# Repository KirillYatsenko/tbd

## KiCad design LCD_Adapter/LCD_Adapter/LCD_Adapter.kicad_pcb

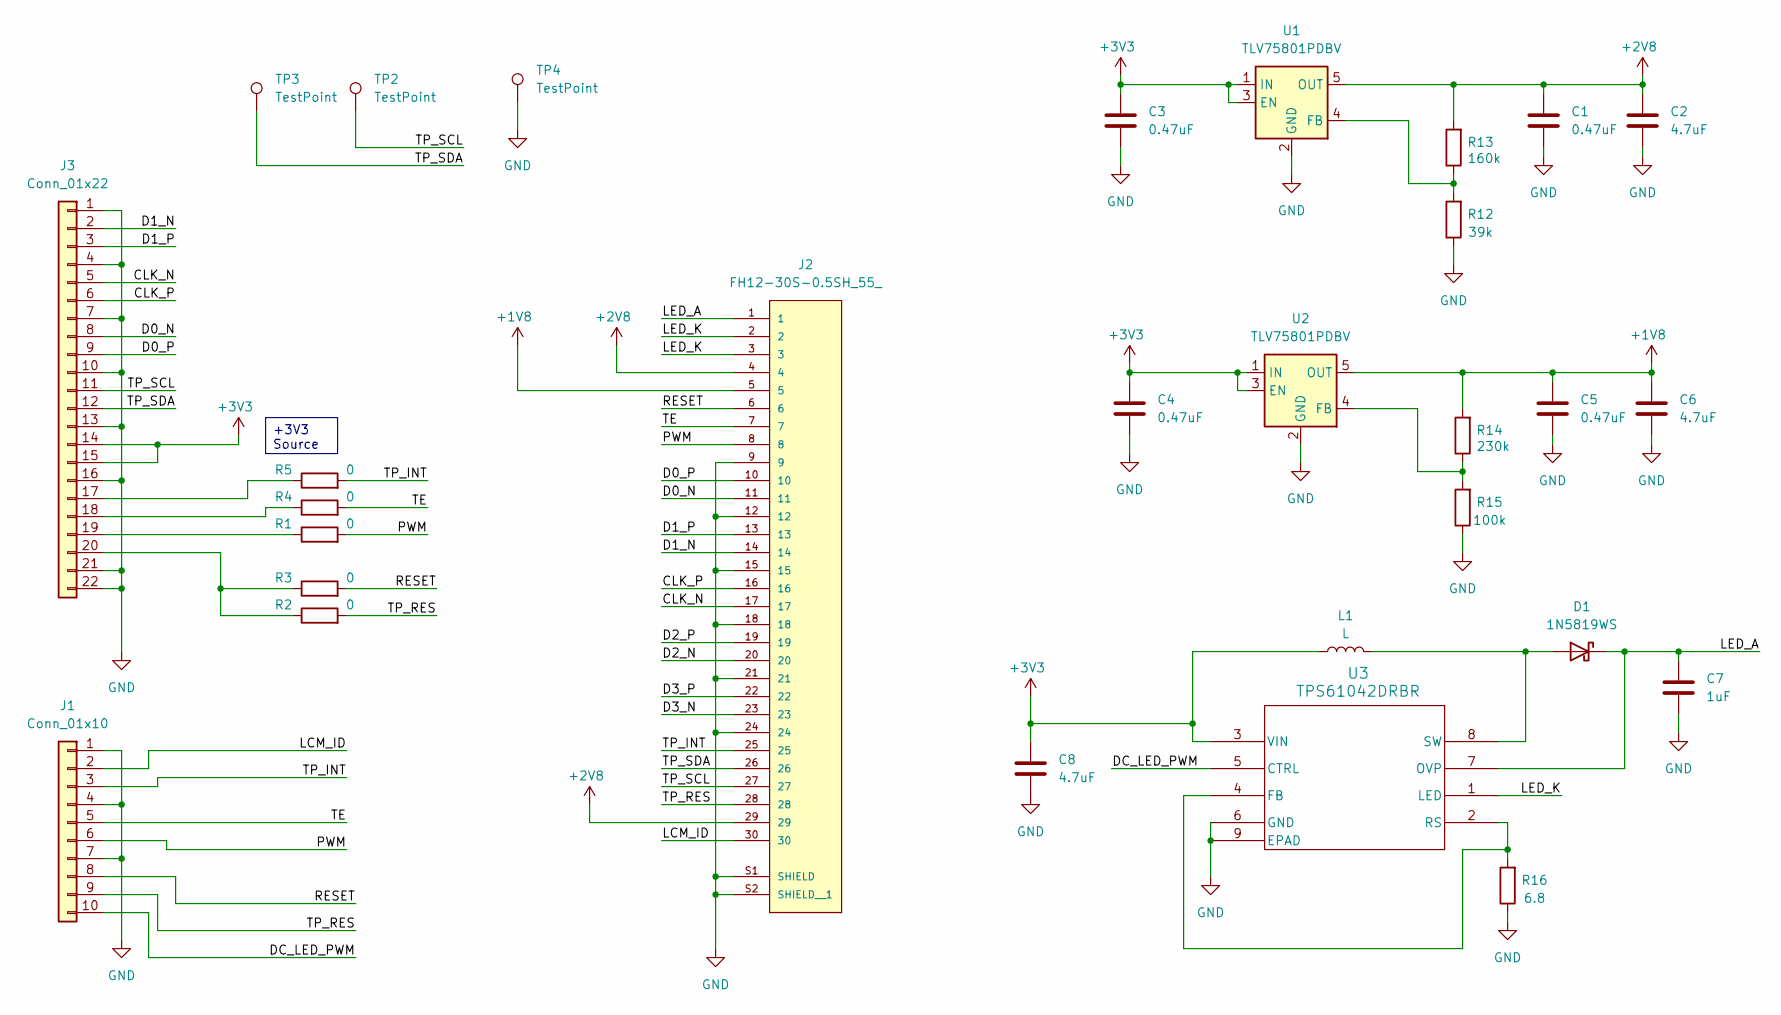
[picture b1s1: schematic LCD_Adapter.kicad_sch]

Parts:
C1, C3, C4, C5: 0.47uF; C_0603_1608Metric
C2, C6, C8: 4.7uF; C_0603_1608Metric
C7: 1uF; C_0603_1608Metric
D1: 1N5819WS; D_SOD-323
J1: Conn_01x10; PinHeader_1x10_P2.54mm_Vertical
J2: FH12-30S-0.5SH_55_; HIROSE_FH12-30S-0.5SH_55_
J3: Conn_01x22; FC-10A20P11H20; LCSC # C23397376
L1: L; L_1210_3225Metric; LCSC # C703083
R1, R2, R3, R4, R5: 0; R_0603_1608Metric
R12: 39k; R_0603_1608Metric
R13: 160k; R_0603_1608Metric
R14: 230k; R_0603_1608Metric
R15: 100k; R_0603_1608Metric
R16: 6.8; R_0603_1608Metric
TP2, TP3, TP4: TestPoint; TestPoint_Pad_D1.0mm
U1, U2: TLV75801PDBV; SOT-23-5
U3: TPS61042DRBR; DRB8_1P75X1P5

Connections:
+1V8: C5.1, C6.1, J2.5, R14.2, U2.5 (OUT)
+2V8: C1.1, C2.1, J2.4, J2.29, R13.2, U1.5 (OUT)
+3V3: C3.1, C4.1, C8.1, J3.14, J3.15, L1.1, U1.1 (IN), U1.3 (EN), U2.1 (IN), U2.3 (EN), U3.3 (VIN)
/ LED_A: C7.1, D1.1 (K), J2.1, U3.7 (OVP)
/ LED_K: J2.2, J2.3, U3.1 (LED)
/CLK_N: J2.17, J3.5
/CLK_P: J2.16, J3.6
/D0_N: J2.11, J3.8
/D0_P: J2.10, J3.9
/D1_N: J2.14, J3.2
/D1_P: J2.13, J3.3
/D2_N: J2.20
/D2_P: J2.19
/D3_N: J2.23
/D3_P: J2.22
/DC_LED_PWM: J1.10, U3.5 (CTRL)
/LCM_ID: J1.2, J2.30
/PWM: J1.6, J2.8, R1.2
/RESET: J1.8, J2.6, R3.2
/TE: J1.5, J2.7, R4.2
/TP_INT: J1.3, J2.25, R5.2
/TP_RES: J1.9, J2.28, R2.2
/TP_SCL: J2.27, J3.11, TP2.1
/TP_SDA: J2.26, J3.12, TP3.1
GND: C1.2, C2.2, C3.2, C4.2, C5.2, C6.2, C7.2, C8.2, J1.1, J1.4, J1.7, J2.9, J2.12, J2.15, J2.18, J2.21, J2.24, J2.S1 (SHIELD), J2.S2 (SHIELD__1), J3.1, J3.4, J3.7, J3.10, J3.13, J3.16, J3.21, J3.22, R12.1, R15.1, R16.1, TP4.1, U1.2 (GND), U2.2 (GND), U3.6 (GND), U3.9 (EPAD)
unnamed: D1.2 (A), L1.2, U3.8 (SW)
unnamed: J3.17, R5.1
unnamed: J3.18, R4.1
unnamed: J3.19, R1.1
unnamed: J3.20, R2.1, R3.1
unnamed: R12.2, R13.1, U1.4 (FB)
unnamed: R14.1, R15.2, U2.4 (FB)
unnamed: R16.2, U3.2 (RS), U3.4 (FB)

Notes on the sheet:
+3V3 Source

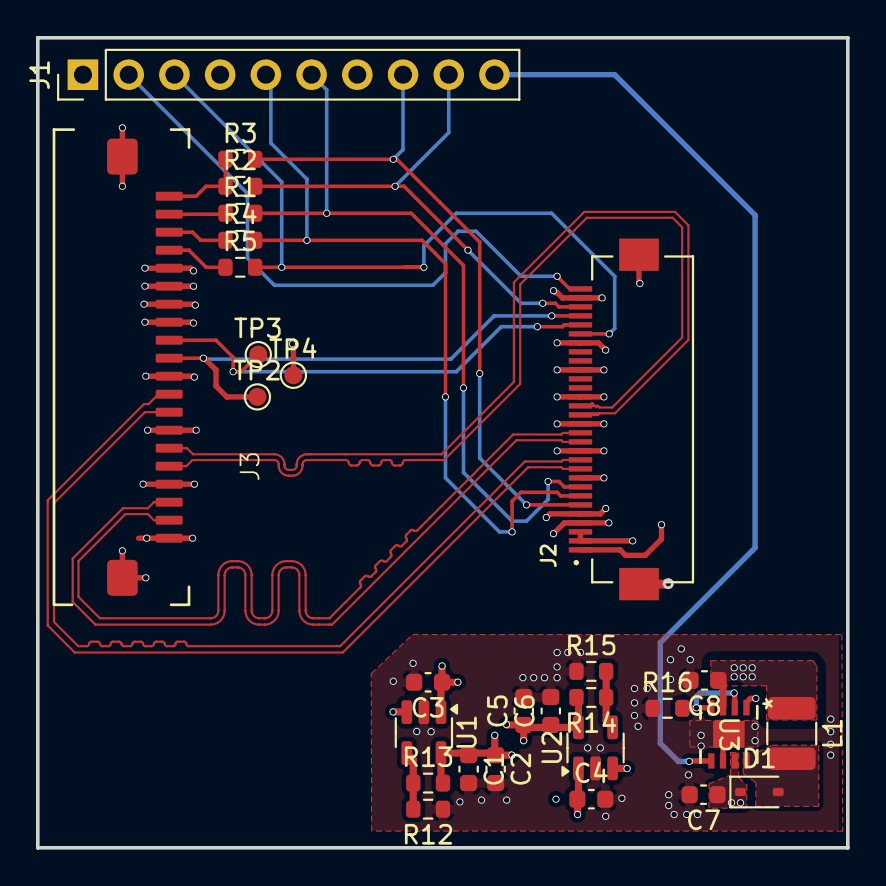
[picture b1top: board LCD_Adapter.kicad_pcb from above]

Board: 4 copper layers, 45.0 x 45.0 mm, 29 parts (0 on the bottom side), 29 nets.

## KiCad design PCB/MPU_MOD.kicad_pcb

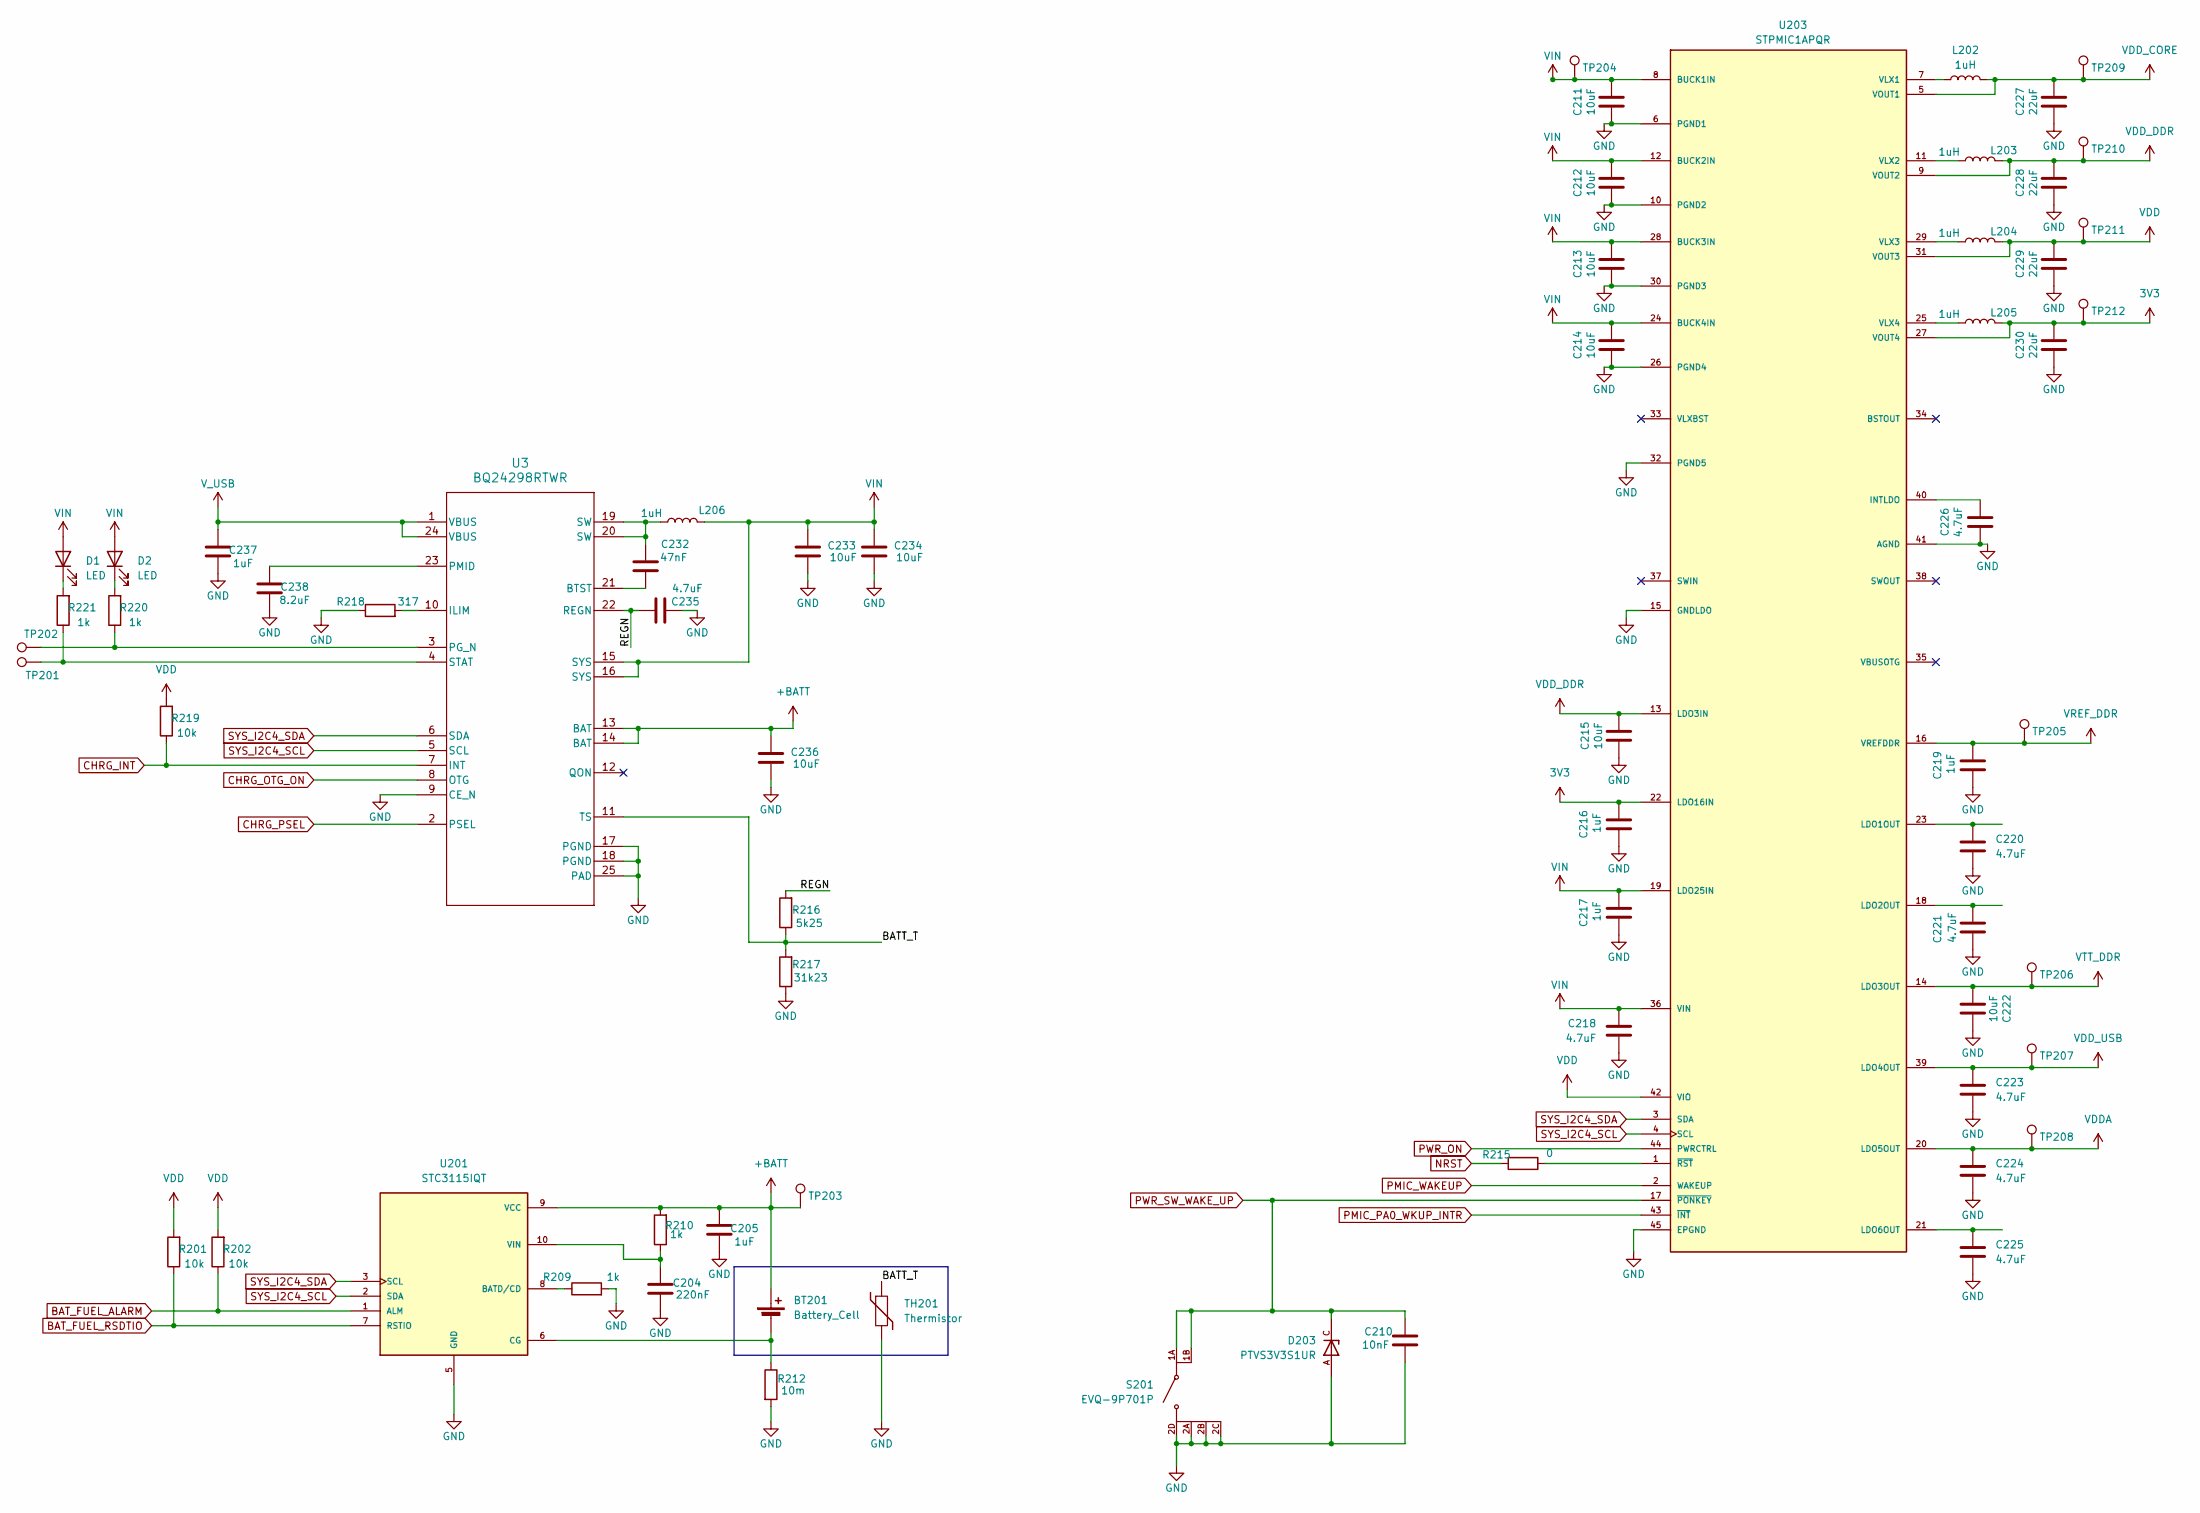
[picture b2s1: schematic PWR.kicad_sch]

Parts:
BT201: Battery_Cell; PinHeader_1x02_P1.00mm_Vertical
C204: 220nF; C_0402_1005Metric
C205, C216, C217, C219, C237: 1uF; C_0402_1005Metric; Mouser P/N 81-GRM155R61E105KA2D
C210: 10nF; C_0402_1005Metric; Mouser P/N 81-GRM155R71C103KA1J
C211, C212, C213, C214, C215, C222, C233, C234, C236: 10uF; C_0603_1608Metric; Mouser P/N 81-GRT188R61A106KE3D
C218, C220, C221, C223, C224, C225, C226, C235: 4.7uF; C_0402_1005Metric; Mouser P/N 81-GRM155R60J475ME7J
C227, C228, C229, C230: 22uF; C_0603_1608Metric; Mouser P/N 81-GRM188R60J226ME0J
C232: 47nF; C_0402_1005Metric
C238: 8.2uF; C_0402_1005Metric
D1, D2: LED; LED_0402_1005Metric
D203: PTVS3V3S1UR; TVS_PTVS3V3S1UR; PARTREV Rev. 3
L202, L203, L204, L205, L206: 1uH; L_1008_2520Metric; Mouser P/N 81-DFE252012P-1R0MP2
R201, R202, R219: 10k; R_0402_1005Metric; Mouser P/N 667-ERJ-3LWFR010V
R209, R210: 1k; R_0402_1005Metric; Mouser P/N 667-ERJ-3LWFR010V
R212: 10m; R_0603_1608Metric; Mouser P/N 667-ERJ-3LWFR010V
R215: 0; R_0402_1005Metric
R216: 5k25; R_0402_1005Metric
R217: 31k23; R_0402_1005Metric
R218: 317; R_0402_1005Metric
R220, R221: 1k; R_0402_1005Metric
S201: EVQ-9P701P; SW_EVQ-9P701P; PARTREV N/A
TH201: Thermistor; PinHeader_1x02_P1.00mm_Vertical
TP201, TP202, TP203, TP204, TP205, TP206, TP207, TP208, TP209, TP210, TP211, TP212: TestPoint; TP_0.5mm
U3: BQ24298RTWR; RTW0024H
U201: STC3115IQT; SON50P300X200X60-10N; PARTREV 9
U203: STPMIC1APQR; QFN40P600X500X80-45N; Mouser P/N 511-STPMIC1APQR

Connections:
3V3: C216.2, C230.2, L205.2, TP212.1, U203.22 (LDO16IN), U203.27 (VOUT4); also elsewhere on the board
+BATT: BT201.1 (+), C205.2, C236.2, R210.2, TP203.1, U3.13 (BAT), U3.14 (BAT), U201.9 (VCC)
/PWR/BATT_T: R216.1, R217.2, TH201.1, U3.11 (TS)
/PWR/REGN: C235.2, R216.2, U3.22 (REGN)
BAT_FUEL_ALARM: R202.1, U201.1 (ALM)
BAT_FUEL_RSDTIO: R201.1, U201.7 (RSTIO)
CHRG_INT: R219.1, U3.7 (INT)
CHRG_OTG_ON: U3.8 (OTG)
CHRG_PSEL: U3.2 (PSEL)
GND: C204.2, C205.1, C210.1, C211.1, C212.1, C213.1, C214.1, C215.1, C216.1, C217.1, C218.1, C219.1, C220.1, C221.1, C222.2, C223.1, C224.1, C225.1, C226.1, C227.1, C228.1, C229.1, C230.1, C233.1, C234.1, C235.1, C236.1, C237.1, C238.1, D203.A, R209.2, R212.2, R217.1, R218.1, S201.2A, S201.2B, S201.2C, S201.2D, TH201.2, U3.9 (CE_N), U3.17 (PGND), U3.18 (PGND), U3.25 (PAD), U201.5 (GND), U203.6 (PGND1), U203.10 (PGND2), U203.15 (GNDLDO), U203.26 (PGND4), U203.30 (PGND3), U203.32 (PGND5), U203.41 (AGND), U203.45 (EPGND); also elsewhere on the board
NRST: R215.2; also elsewhere on the board
unnamed: BT201.2 (-), R212.1, U201.6 (CG)
unnamed: C232.1, L206.1, U3.19 (SW), U3.20 (SW)
unnamed: D1.1 (K), R221.2
unnamed: D2.1 (K), R220.2
unnamed: C232.2, U3.21 (BTST)
unnamed: R218.2, U3.10 (ILIM)
unnamed: R220.1, TP202.1, U3.3 (PG_N)
unnamed: C238.2, U3.23 (PMID)
unnamed: R221.1, TP201.1, U3.4 (STAT)
unnamed: R209.1, U201.8 (BATD/CD)
unnamed: C204.1, R210.1, U201.10 (VIN)
unnamed: C226.2, U203.40 (INTLDO)
unnamed: C220.2, U203.23 (LDO1OUT)
unnamed: C221.2, U203.18 (LDO2OUT)
unnamed: C225.2, U203.21 (LDO6OUT)
unnamed: L202.1, U203.7 (VLX1)
unnamed: L203.1, U203.11 (VLX2)
unnamed: L204.1, U203.29 (VLX3)
unnamed: L205.1, U203.25 (VLX4)
unnamed: R215.1, U203.1 (~RST)
PMIC_PA0_WKUP_INTR: U203.43 (~INT); also elsewhere on the board
PMIC_WAKEUP: U203.2 (WAKEUP)
PWR_ON: U203.44 (PWRCTRL); also elsewhere on the board
PWR_SW_WAKE_UP: C210.2, D203.C, S201.1A, S201.1B, U203.17 (~PONKEY); also elsewhere on the board
SYS_I2C4_SCL: U3.5 (SCL), U201.2 (SDA), U203.4 (SCL); also elsewhere on the board
SYS_I2C4_SDA: U3.6 (SDA), U201.3 (SCL), U203.3 (SDA); also elsewhere on the board
VDD: C229.2, L204.2, R201.2, R202.2, R219.2, TP211.1, U203.31 (VOUT3), U203.42 (VIO); also elsewhere on the board
VDDA: C224.2, TP208.1, U203.20 (LDO5OUT)
VDD_CORE: C227.2, L202.2, TP209.1, U203.5 (VOUT1); also elsewhere on the board
VDD_DDR: C215.2, C228.2, L203.2, TP210.1, U203.9 (VOUT2), U203.13 (LDO3IN); also elsewhere on the board
VDD_USB: C223.2, TP207.1, U203.39 (LDO4OUT); also elsewhere on the board
VIN: C211.2, C212.2, C213.2, C214.2, C217.2, C218.2, C233.2, C234.2, D1.2 (A), D2.2 (A), L206.2, TP204.1, U3.15 (SYS), U3.16 (SYS), U203.8 (BUCK1IN), U203.12 (BUCK2IN), U203.19 (LDO25IN), U203.24 (BUCK4IN), U203.28 (BUCK3IN), U203.36 (VIN)
VREF_DDR: C219.2, TP205.1, U203.16 (VREFDDR); also elsewhere on the board
VTT_DDR: C222.1, TP206.1, U203.14 (LDO3OUT); also elsewhere on the board
V_USB: C237.2, U3.1 (VBUS), U3.24 (VBUS); also elsewhere on the board

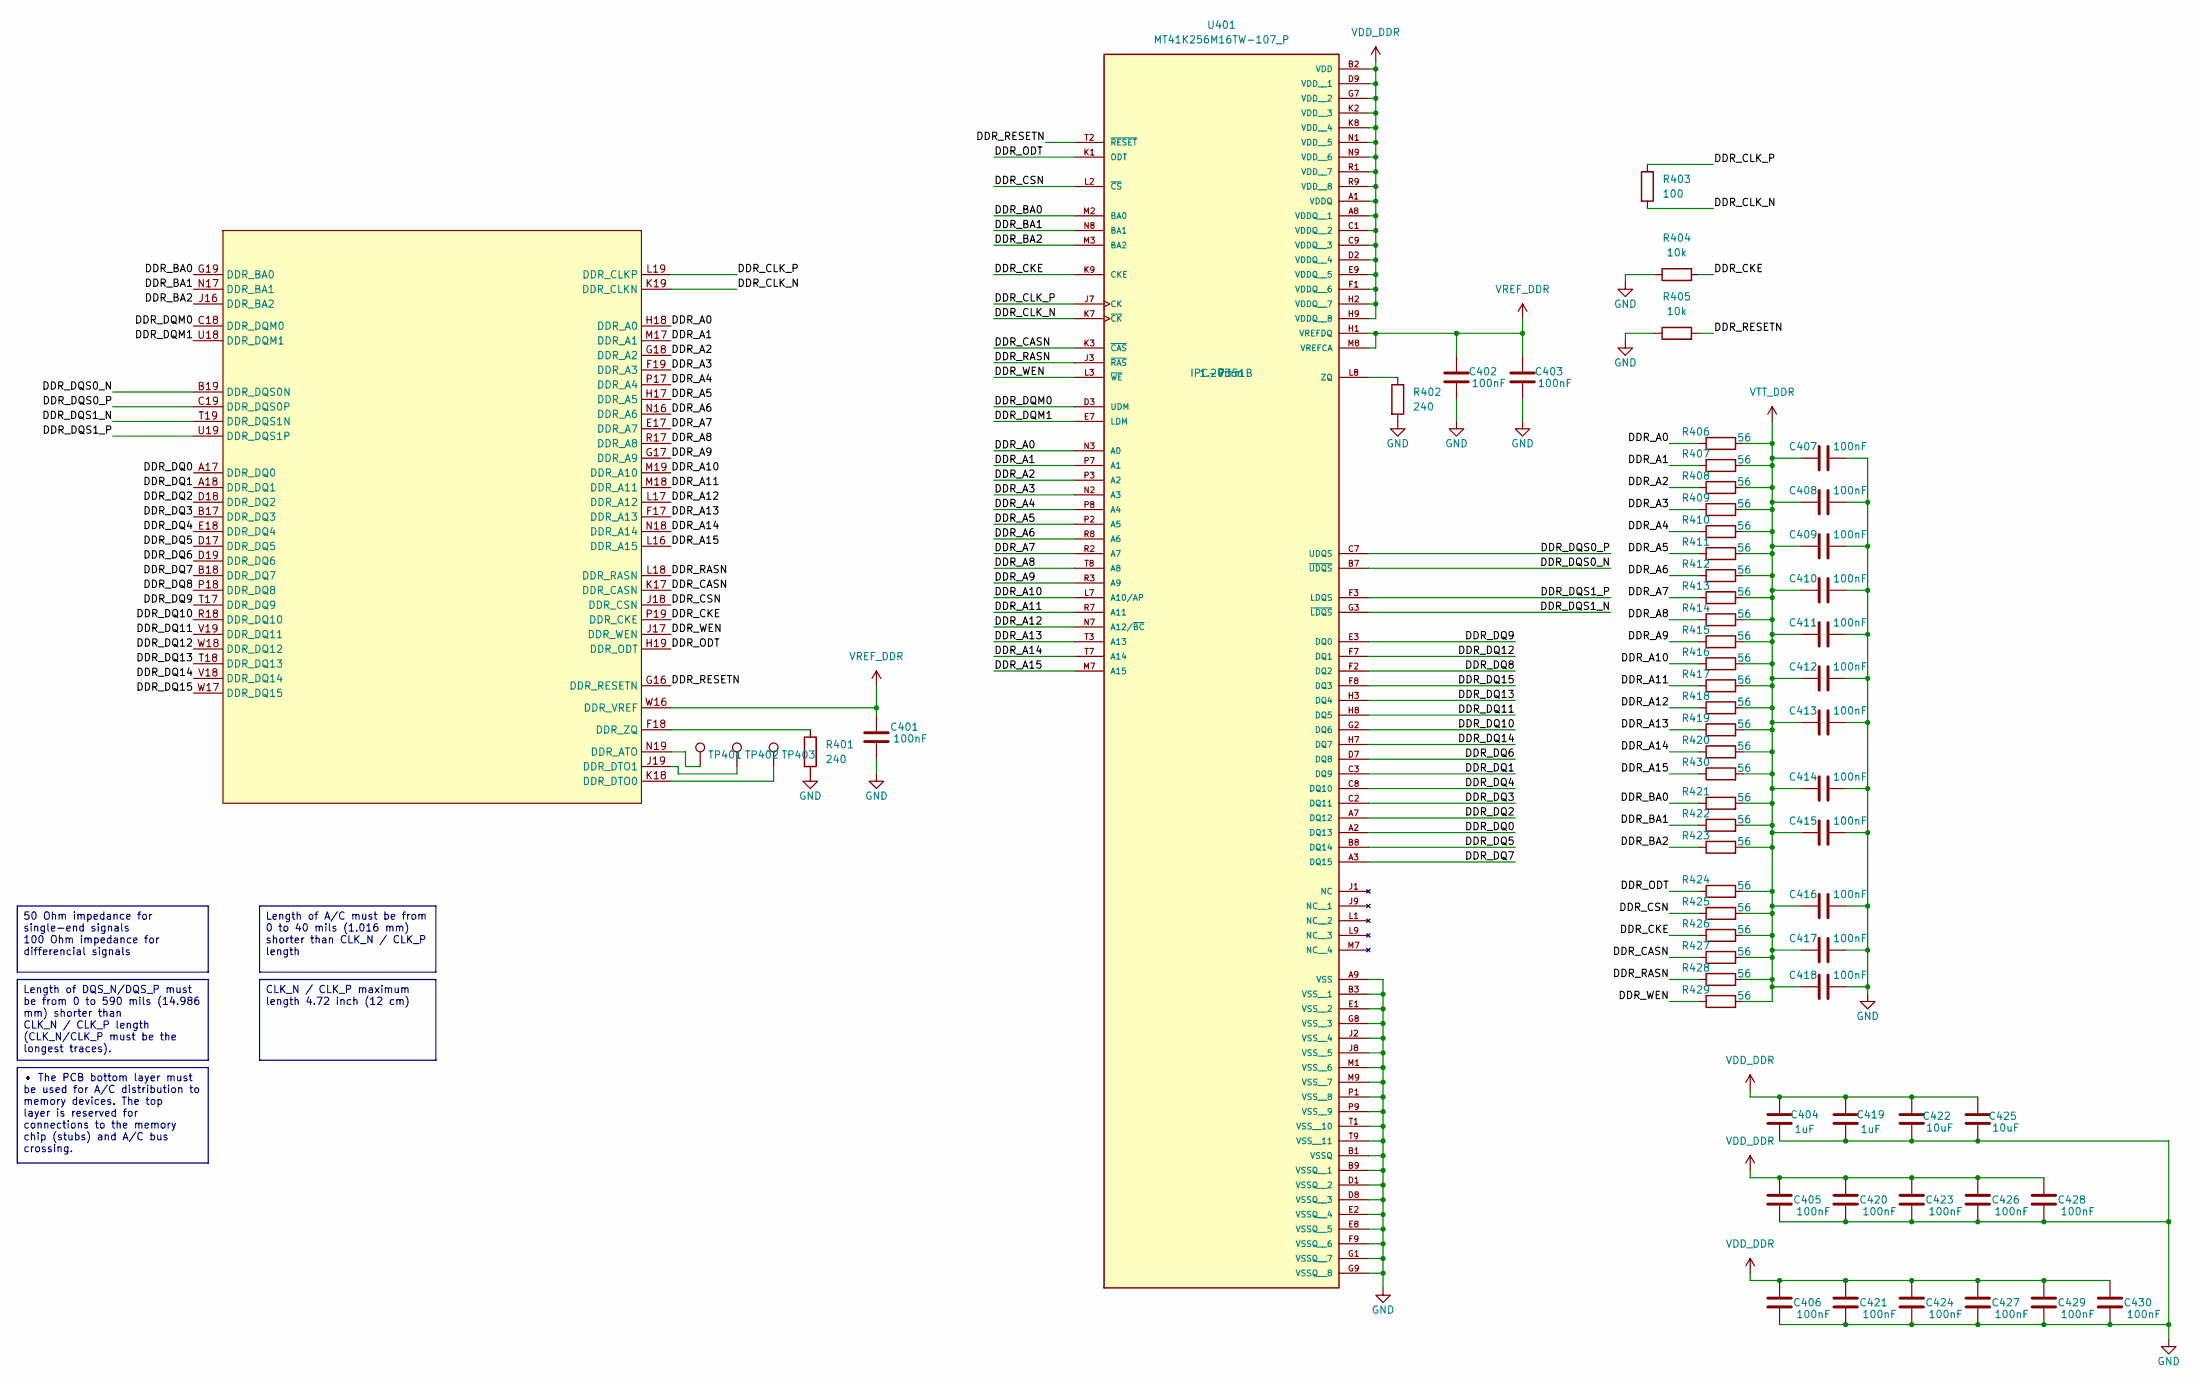
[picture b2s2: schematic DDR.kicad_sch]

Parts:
C401, C402, C403, C405, C406, C407, C408, C409, C410, C411, C412, C413, C414, C415, C416, C417, C418, C420, C421, C423, C424, C426, C427, C428, C429, C430: 100nF; C_0402_1005Metric; Mouser P/N 81-GRM155R61E104KA7J
C404, C419: 1uF; C_0402_1005Metric; Mouser P/N 81-GRM155R61E105KA2D
C422, C425: 10uF; C_0603_1608Metric; Mouser P/N 81-GRT188R61A106KE3D
R401, R402: 240; R_0402_1005Metric
R403: 100; R_0402_1005Metric
R404, R405: 10k; R_0402_1005Metric
R406, R407, R408, R409, R410, R411, R412, R413, R414, R415, R416, R417, R418, R419, R420, R421, R422, R423, R424, R425, R426, R427, R428, R429, R430: 56; R_0402_1005Metric
TP401, TP402, TP403: TestPoint; TP_0.5mm
U301: STM32MP157FABx; ST_LFBGA-354_16x16mm_Layout19x19_P0.8mm
U401: MT41K256M16TW-107_P; BGA96C80P9X16_1400X800X120; Mouser P/N 340-265846-TRAY

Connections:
/DDR/DDR_A0: R406.1, U301.H18 (DDR_A0), U401.N3 (A0)
/DDR/DDR_A1: R407.1, U301.M17 (DDR_A1), U401.P7 (A1)
/DDR/DDR_A2: R408.1, U301.G18 (DDR_A2), U401.P3 (A2)
/DDR/DDR_A3: R409.1, U301.F19 (DDR_A3), U401.N2 (A3)
/DDR/DDR_A4: R410.1, U301.P17 (DDR_A4), U401.P8 (A4)
/DDR/DDR_A5: R411.1, U301.H17 (DDR_A5), U401.P2 (A5)
/DDR/DDR_A6: R412.1, U301.N16 (DDR_A6), U401.R8 (A6)
/DDR/DDR_A7: R413.1, U301.E17 (DDR_A7), U401.R2 (A7)
/DDR/DDR_A8: R414.1, U301.R17 (DDR_A8), U401.T8 (A8)
/DDR/DDR_A9: R415.1, U301.G17 (DDR_A9), U401.R3 (A9)
/DDR/DDR_A10: R416.1, U301.M19 (DDR_A10), U401.L7 (A10/AP)
/DDR/DDR_A11: R417.1, U301.M18 (DDR_A11), U401.R7 (A11)
/DDR/DDR_A12: R418.1, U301.L17 (DDR_A12), U401.N7 (A12/~BC)
/DDR/DDR_A13: R419.1, U301.F17 (DDR_A13), U401.T3 (A13)
/DDR/DDR_A14: R420.1, U301.N18 (DDR_A14), U401.T7 (A14)
/DDR/DDR_A15: R430.1, U301.L16 (DDR_A15), U401.M7 (A15)
/DDR/DDR_BA0: R421.1, U301.G19 (DDR_BA0), U401.M2 (BA0)
/DDR/DDR_BA1: R422.1, U301.N17 (DDR_BA1), U401.N8 (BA1)
/DDR/DDR_BA2: R423.1, U301.J16 (DDR_BA2), U401.M3 (BA2)
/DDR/DDR_CASN: R427.1, U301.K17 (DDR_CASN), U401.K3 (~CAS)
/DDR/DDR_CKE: R404.2, R426.1, U301.P19 (DDR_CKE), U401.K9 (CKE)
/DDR/DDR_CLK_N: R403.2, U301.K19 (DDR_CLKN), U401.K7 (~CK)
/DDR/DDR_CLK_P: R403.1, U301.L19 (DDR_CLKP), U401.J7 (CK)
/DDR/DDR_CSN: R425.1, U301.J18 (DDR_CSN), U401.L2 (~CS)
/DDR/DDR_DQ0: U301.A17 (DDR_DQ0), U401.A2 (DQ13)
/DDR/DDR_DQ1: U301.A18 (DDR_DQ1), U401.C3 (DQ9)
/DDR/DDR_DQ2: U301.D18 (DDR_DQ2), U401.A7 (DQ12)
/DDR/DDR_DQ3: U301.B17 (DDR_DQ3), U401.C2 (DQ11)
/DDR/DDR_DQ4: U301.E18 (DDR_DQ4), U401.C8 (DQ10)
/DDR/DDR_DQ5: U301.D17 (DDR_DQ5), U401.B8 (DQ14)
/DDR/DDR_DQ6: U301.D19 (DDR_DQ6), U401.D7 (DQ8)
/DDR/DDR_DQ7: U301.B18 (DDR_DQ7), U401.A3 (DQ15)
/DDR/DDR_DQ8: U301.P18 (DDR_DQ8), U401.F2 (DQ2)
/DDR/DDR_DQ9: U301.T17 (DDR_DQ9), U401.E3 (DQ0)
/DDR/DDR_DQ10: U301.R18 (DDR_DQ10), U401.G2 (DQ6)
/DDR/DDR_DQ11: U301.V19 (DDR_DQ11), U401.H8 (DQ5)
/DDR/DDR_DQ12: U301.W18 (DDR_DQ12), U401.F7 (DQ1)
/DDR/DDR_DQ13: U301.T18 (DDR_DQ13), U401.H3 (DQ4)
/DDR/DDR_DQ14: U301.V18 (DDR_DQ14), U401.H7 (DQ7)
/DDR/DDR_DQ15: U301.W17 (DDR_DQ15), U401.F8 (DQ3)
/DDR/DDR_DQM0: U301.C18 (DDR_DQM0), U401.D3 (UDM)
/DDR/DDR_DQM1: U301.U18 (DDR_DQM1), U401.E7 (LDM)
/DDR/DDR_DQS0_N: U301.B19 (DDR_DQS0N), U401.B7 (~UDQS)
/DDR/DDR_DQS0_P: U301.C19 (DDR_DQS0P), U401.C7 (UDQS)
/DDR/DDR_DQS1_N: U301.T19 (DDR_DQS1N), U401.G3 (~LDQS)
/DDR/DDR_DQS1_P: U301.U19 (DDR_DQS1P), U401.F3 (LDQS)
/DDR/DDR_ODT: R424.1, U301.H19 (DDR_ODT), U401.K1 (ODT)
/DDR/DDR_RASN: R428.1, U301.L18 (DDR_RASN), U401.J3 (~RAS)
/DDR/DDR_RESETN: R405.2, U301.G16 (DDR_RESETN), U401.T2 (~RESET)
/DDR/DDR_WEN: R429.1, U301.J17 (DDR_WEN), U401.L3 (~WE)
GND: C401.1, C402.2, C403.2, C404.2, C405.1, C406.1, C407.2, C408.2, C409.2, C410.2, C411.2, C412.2, C413.2, C414.2, C415.2, C416.2, C417.2, C418.2, C419.2, C420.1, C421.1, C422.1, C423.1, C424.1, C425.1, C426.1, C427.1, C428.1, C429.1, C430.1, R401.2, R402.2, R404.1, R405.1, U401.A9 (VSS), U401.B1 (VSSQ), U401.B3 (VSS__1), U401.B9 (VSSQ__1), U401.D1 (VSSQ__2), U401.D8 (VSSQ__3), U401.E1 (VSS__2), U401.E2 (VSSQ__4), U401.E8 (VSSQ__5), U401.F9 (VSSQ__6), U401.G1 (VSSQ__7), U401.G8 (VSS__3), U401.G9 (VSSQ__8), U401.J2 (VSS__4), U401.J8 (VSS__5), U401.M1 (VSS__6), U401.M9 (VSS__7), U401.P1 (VSS__8), U401.P9 (VSS__9), U401.T1 (VSS__10), U401.T9 (VSS__11); also elsewhere on the board
unnamed: TP401.1, U301.N19 (DDR_ATO)
unnamed: TP403.1, U301.K18 (DDR_DTO0)
unnamed: TP402.1, U301.J19 (DDR_DTO1)
unnamed: R401.1, U301.F18 (DDR_ZQ)
unnamed: R402.1, U401.L8 (ZQ)
VDD_DDR: C404.1, C405.2, C406.2, C419.1, C420.2, C421.2, C422.2, C423.2, C424.2, C425.2, C426.2, C427.2, C428.2, C429.2, C430.2, U401.A1 (VDDQ), U401.A8 (VDDQ__1), U401.B2 (VDD), U401.C1 (VDDQ__2), U401.C9 (VDDQ__3), U401.D2 (VDDQ__4), U401.D9 (VDD__1), U401.E9 (VDDQ__5), U401.F1 (VDDQ__6), U401.G7 (VDD__2), U401.H2 (VDDQ__7), U401.H9 (VDDQ__8), U401.K2 (VDD__3), U401.K8 (VDD__4), U401.N1 (VDD__5), U401.N9 (VDD__6), U401.R1 (VDD__7), U401.R9 (VDD__8); also elsewhere on the board
VREF_DDR: C401.2, C402.1, C403.1, U301.W16 (DDR_VREF), U401.H1 (VREFDQ), U401.M8 (VREFCA); also elsewhere on the board
VTT_DDR: C407.1, C408.1, C409.1, C410.1, C411.1, C412.1, C413.1, C414.1, C415.1, C416.1, C417.1, C418.1, R406.2, R407.2, R408.2, R409.2, R410.2, R411.2, R412.2, R413.2, R414.2, R415.2, R416.2, R417.2, R418.2, R419.2, R420.2, R421.2, R422.2, R423.2, R424.2, R425.2, R426.2, R427.2, R428.2, R429.2, R430.2; also elsewhere on the board

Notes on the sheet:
Length of DQS_N/DQS_P must be from 0 to 590 mils (14.986 mm) shorter than CLK_N / CLK_P length (CLK_N/CLK_P must be the longest traces).
• The PCB bottom layer must be used for A/C distribution to memory devices. The top layer is reserved for connections to the memory chip (stubs) and A/C bus crossing.
CLK_N / CLK_P maximum length 4.72 inch (12 cm)
50 Ohm impedance for single-end signals 100 Ohm impedance for differencial signals
Length of A/C must be from 0 to 40 mils (1.016 mm) shorter than CLK_N / CLK_P length

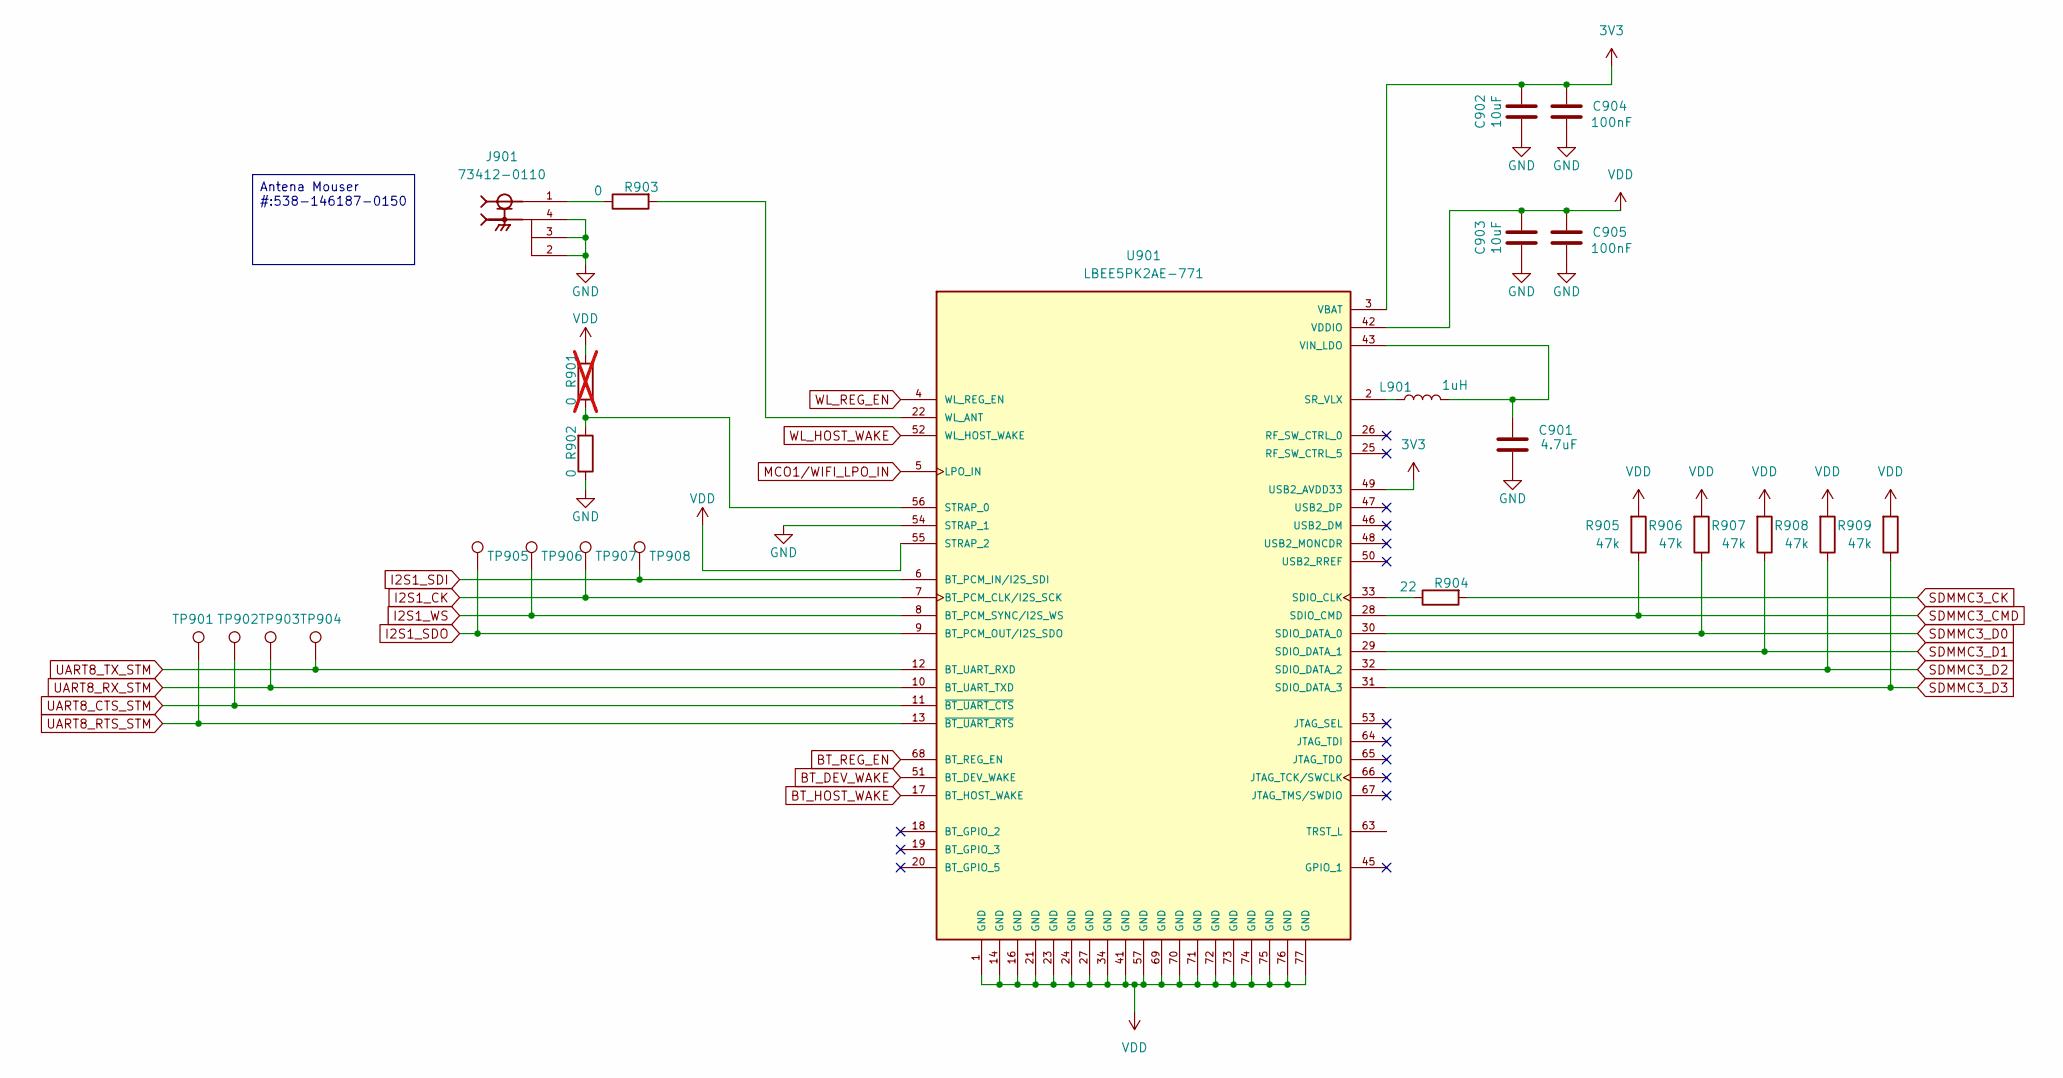
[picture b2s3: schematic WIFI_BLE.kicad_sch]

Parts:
C901: 4.7uF; C_0402_1005Metric; Mouser P/N 81-GRM155R60J475ME7J
C902, C903: 10uF; C_0603_1608Metric; Mouser P/N 81-GRT188R61A106KE3D
C904, C905: 100nF; C_0402_1005Metric; Mouser P/N 81-GRM155R61E104KA7J
J901: 73412-0110; MOLEX_73412-0110; PARTREV D
L901: 1uH; L_Murata_DFE201610P; Mouser P/N 81-DFE201612E-2R2MP2
R901: 0; R_0402_1005Metric; not fitted
R902, R903: 0; R_0402_1005Metric
R904: 22; R_0402_1005Metric
R905, R906, R907, R908, R909: 47k; R_0402_1005Metric
TP901, TP902, TP903, TP904, TP905, TP906, TP907, TP908: TestPoint; TP_0.5mm
U901: LBEE5PK2AE-771; XCVR_LBEE5PK2AE-771; PARTREV E

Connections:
3V3: C902.2, C904.2, U901.3 (VBAT), U901.49 (USB2_AVDD33); also elsewhere on the board
BT_DEV_WAKE: U901.51 (BT_DEV_WAKE)
BT_HOST_WAKE: U901.17 (BT_HOST_WAKE)
BT_REG_EN: U901.68 (BT_REG_EN)
GND: C901.1, C902.1, C903.1, C904.1, C905.1, J901.2, J901.3, J901.4, R902.1, U901.54 (STRAP_1); also elsewhere on the board
I2S1_CK: TP907.1, U901.7 (BT_PCM_CLK/I2S_SCK); also elsewhere on the board
I2S1_SDI: TP908.1, U901.6 (BT_PCM_IN/I2S_SDI); also elsewhere on the board
I2S1_SDO: TP905.1, U901.9 (BT_PCM_OUT/I2S_SDO); also elsewhere on the board
I2S1_WS: TP906.1, U901.8 (BT_PCM_SYNC/I2S_WS); also elsewhere on the board
MCO1/WIFI_LPO_IN: U901.5 (LPO_IN)
unnamed: J901.1, R903.1
unnamed: R904.1, U901.33 (SDIO_CLK)
unnamed: L901.1, U901.2 (SR_VLX)
unnamed: R901.1, R902.2, U901.56 (STRAP_0)
unnamed: C901.2, L901.2, U901.43 (VIN_LDO)
unnamed: R903.2, U901.22 (WL_ANT)
SDMMC3_CK: R904.2; also elsewhere on the board
SDMMC3_CMD: R905.1, U901.28 (SDIO_CMD); also elsewhere on the board
SDMMC3_D0: R906.1, U901.30 (SDIO_DATA_0); also elsewhere on the board
SDMMC3_D1: R907.1, U901.29 (SDIO_DATA_1); also elsewhere on the board
SDMMC3_D2: R908.1, U901.32 (SDIO_DATA_2); also elsewhere on the board
SDMMC3_D3: R909.1, U901.31 (SDIO_DATA_3); also elsewhere on the board
UART8_CTS_STM: TP902.1, U901.11 (~BT_UART_CTS); also elsewhere on the board
UART8_RTS_STM: TP901.1, U901.13 (~BT_UART_RTS); also elsewhere on the board
UART8_RX_STM: TP903.1, U901.10 (BT_UART_TXD); also elsewhere on the board
UART8_TX_STM: TP904.1, U901.12 (BT_UART_RXD); also elsewhere on the board
VDD: C903.2, C905.2, R901.2, R905.2, R906.2, R907.2, R908.2, R909.2, U901.1 (GND), U901.14 (GND), U901.16 (GND), U901.21 (GND), U901.23 (GND), U901.24 (GND), U901.27 (GND), U901.34 (GND), U901.41 (GND), U901.42 (VDDIO), U901.55 (STRAP_2), U901.57 (GND), U901.69 (GND), U901.70 (GND), U901.71 (GND), U901.72 (GND), U901.73 (GND), U901.74 (GND), U901.75 (GND), U901.76 (GND), U901.77 (GND); also elsewhere on the board
WL_HOST_WAKE: U901.52 (WL_HOST_WAKE)
WL_REG_EN: U901.4 (WL_REG_EN)

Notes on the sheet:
Antena Mouser #:538-146187-0150

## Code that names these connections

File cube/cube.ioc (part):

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Mcu.Name=STM32MP157FABx
Mcu.Package=LFBGA354
Mcu.UserName=STM32MP157FABx
PA0.Mode=WakeUp1
PA0.Signal=PWR_WKUP1
PA13.Mode=Clock-out-1
PA13.Signal=RCC_MCO_1
PA2.Mode=WakeUp2
PA2.Signal=PWR_WKUP2
PA4.Mode=Full_Duplex_Master
PA4.Signal=I2S1_WS
PA5.Mode=Full_Duplex_Master
PA5.Signal=I2S1_CK
PA6.Mode=Full_Duplex_Master
PA6.Signal=I2S1_SDI
PA7.Mode=Full_Duplex_Master
PA7.Signal=I2S1_SDO
PA8.Mode=mmc_8_bits_Wide_bus
PA8.Signal=SDMMC2_D4
PA9.Mode=mmc_8_bits_Wide_bus
PA9.Signal=SDMMC2_D5
PB10.Mode=Full_Duplex_Master
PB10.Signal=I2S2_CK
PB12.Mode=Full_Duplex_Master
PB12.Signal=I2S2_WS
PB14.Mode=mmc_8_bits_Wide_bus
PB14.Signal=SDMMC2_D0
PB15.Mode=mmc_8_bits_Wide_bus
PB15.Signal=SDMMC2_D1
PB2.Mode=Asynchronous
PB2.Signal=UART4_RX
PB3.Mode=mmc_8_bits_Wide_bus
PB3.Signal=SDMMC2_D2
PB4.Mode=mmc_8_bits_Wide_bus
PB4.Signal=SDMMC2_D3
PB6.Mode=I2C
PB6.Signal=I2C4_SCL
PC1.Mode=Full_Duplex_Master
PC1.Signal=I2S2_SDO
PC10.Mode=SD_4_bits_Wide_bus
PC10.Signal=SDMMC1_D2
PC11.Mode=SD_4_bits_Wide_bus
PC11.Signal=SDMMC1_D3
PC12.Mode=SD_4_bits_Wide_bus
PC12.Signal=SDMMC1_CK
PC14-OSC32_IN.Mode=LSE-External-Oscillator
PC14-OSC32_IN.Signal=RCC_OSC32_IN
PC15-OSC32_OUT.Mode=LSE-External-Oscillator
PC15-OSC32_OUT.Signal=RCC_OSC32_OUT
PC2.Mode=Full_Duplex_Master
PC2.Signal=I2S2_SDI
PC8.Mode=SD_4_bits_Wide_bus
PC8.Signal=SDMMC1_D0
PC9.Mode=SD_4_bits_Wide_bus
PC9.Signal=SDMMC1_D1
PD0.Mode=SD_4_bits_Wide_bus
PD0.Signal=SDMMC3_CMD
PD1.Mode=SD_4_bits_Wide_bus
PD1.Signal=SDMMC3_D0
PD13.Mode=I2C
PD13.Signal=I2C4_SDA
PD2.Mode=SD_4_bits_Wide_bus
PD2.Signal=SDMMC1_CMD
PD3.Mode=mmc_8_bits_Wide_bus
PD3.Signal=SDMMC2_D7
PD4.Mode=SD_4_bits_Wide_bus
PD4.Signal=SDMMC3_D1
PD5.Mode=SD_4_bits_Wide_bus
PD5.Signal=SDMMC3_D2
PD7.Mode=SD_4_bits_Wide_bus
PD7.Signal=SDMMC3_D3
PE0.Mode=Asynchronous
PE0.Signal=UART8_RX
PE1.Mode=Asynchronous
PE1.Signal=UART8_TX
PE14.Mode=CTS_RTS
PE14.Signal=UART8_RTS
PE15.Mode=CTS_RTS
PE15.Signal=UART8_CTS
PE3.Mode=mmc_8_bits_Wide_bus
PE3.Signal=SDMMC2_CK
PE5.Mode=mmc_8_bits_Wide_bus
PE5.Signal=SDMMC2_D6
PG11.Mode=Asynchronous
PG11.Signal=UART4_TX
PG15.Mode=SD_4_bits_Wide_bus
PG15.Signal=SDMMC3_CK
PG6.Mode=mmc_8_bits_Wide_bus
PG6.Signal=SDMMC2_CMD
PH0-OSC_IN.Mode=HSE-External-Oscillator
PH0-OSC_IN.Signal=RCC_OSC_IN
PH1-OSC_OUT.Mode=HSE-External-Oscillator
PH1-OSC_OUT.Signal=RCC_OSC_OUT
RCC.HSE_VALUE=24000000
board=custom

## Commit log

2025-04-05 docs: Create simple github page for collaboration
    Following: "Creating a GitHub Pages site with Jekyll" on GitHub docs
2025-04-05 docs: Add overall hardware/software design goals
    A lot of things still requires better description.
    But for initial PoC it should be all right.
2025-04-17 added pcb repo. MPU sumbol, rev doc
2025-04-17 pcb update
2025-04-17 PCB_UPDATE
2025-04-17 Rename README.txt to README.md
2025-04-17 Rename README.txt to README.mb
2025-04-17 Rename README.mb to README.md
2025-04-17 DTS generated by cubeimx only for look
2025-04-22 PCB_UPDATE. PWR DONE, DDR STARTED
2025-04-22 DDR_DONE
2025-04-23 added Dustin's review pdf for MMU power
2025-04-23 Look like MPU done
2025-04-29 added eMMC
2025-05-02 wifi done
2025-05-02 added Cube
2025-05-10 ADDED PCB FROM STM
2025-06-04 PCD_UPDATE
2025-06-14 PSB_ADAPTER UPDATE

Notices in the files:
parts and their libraries:
COPYRIGHT: Copyright (C) 2018 Accelerated Designs. All rights reserved
